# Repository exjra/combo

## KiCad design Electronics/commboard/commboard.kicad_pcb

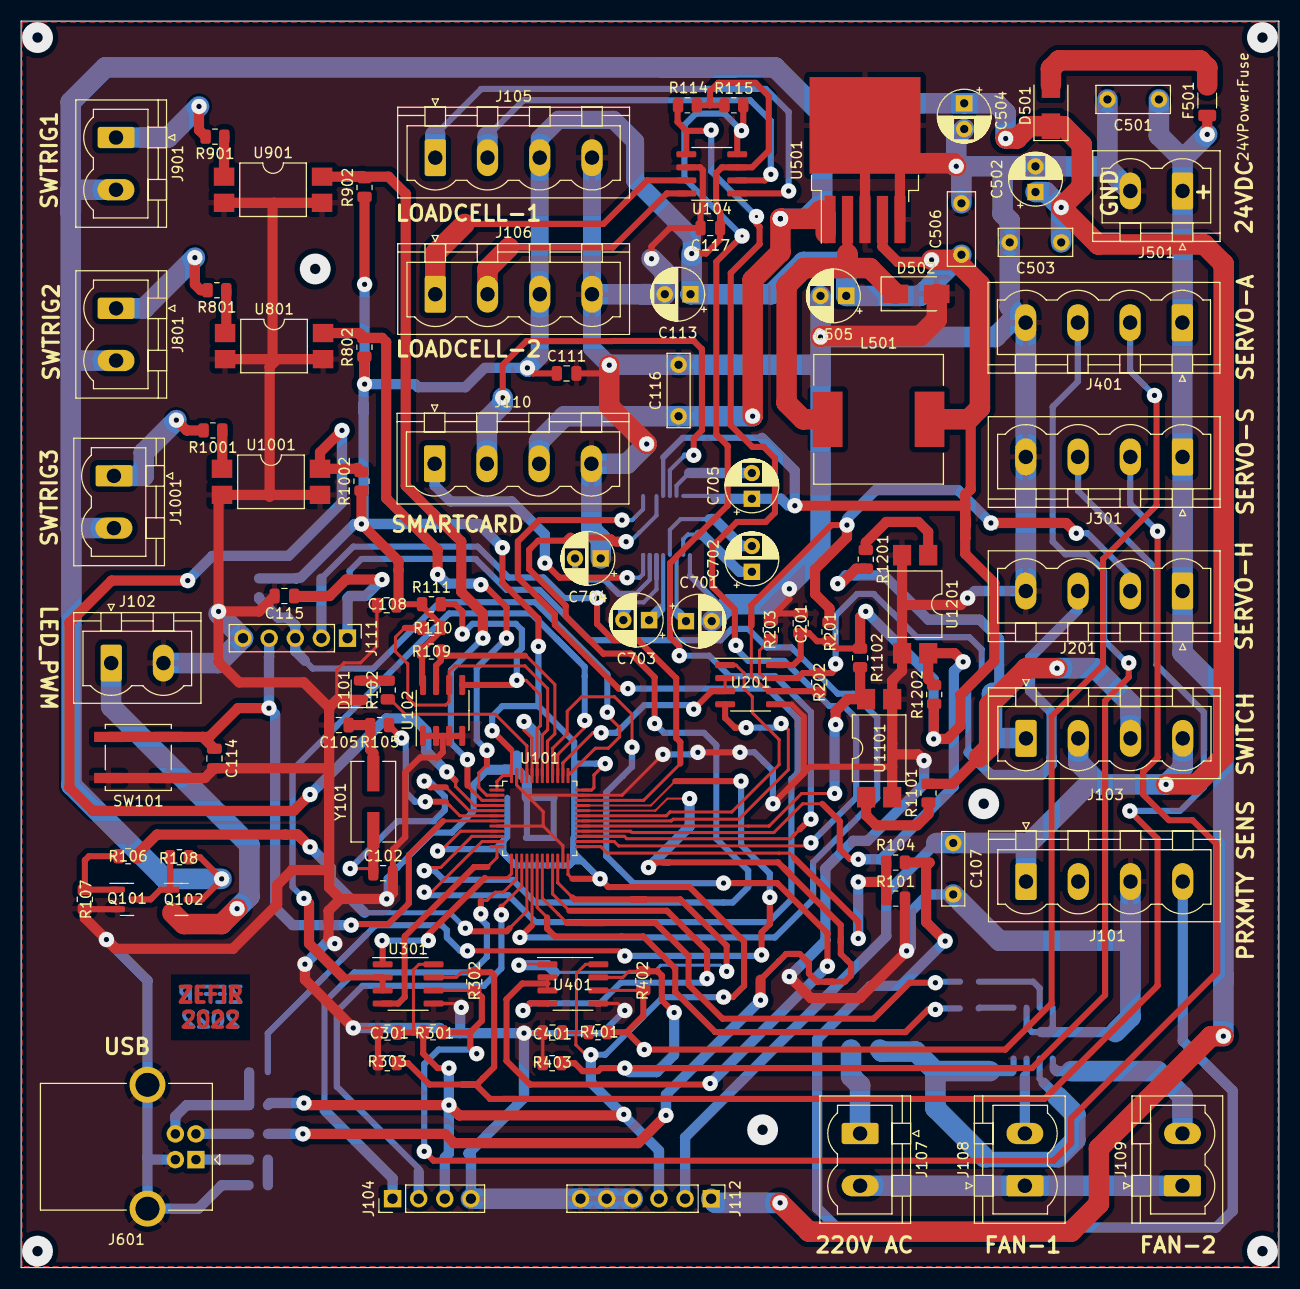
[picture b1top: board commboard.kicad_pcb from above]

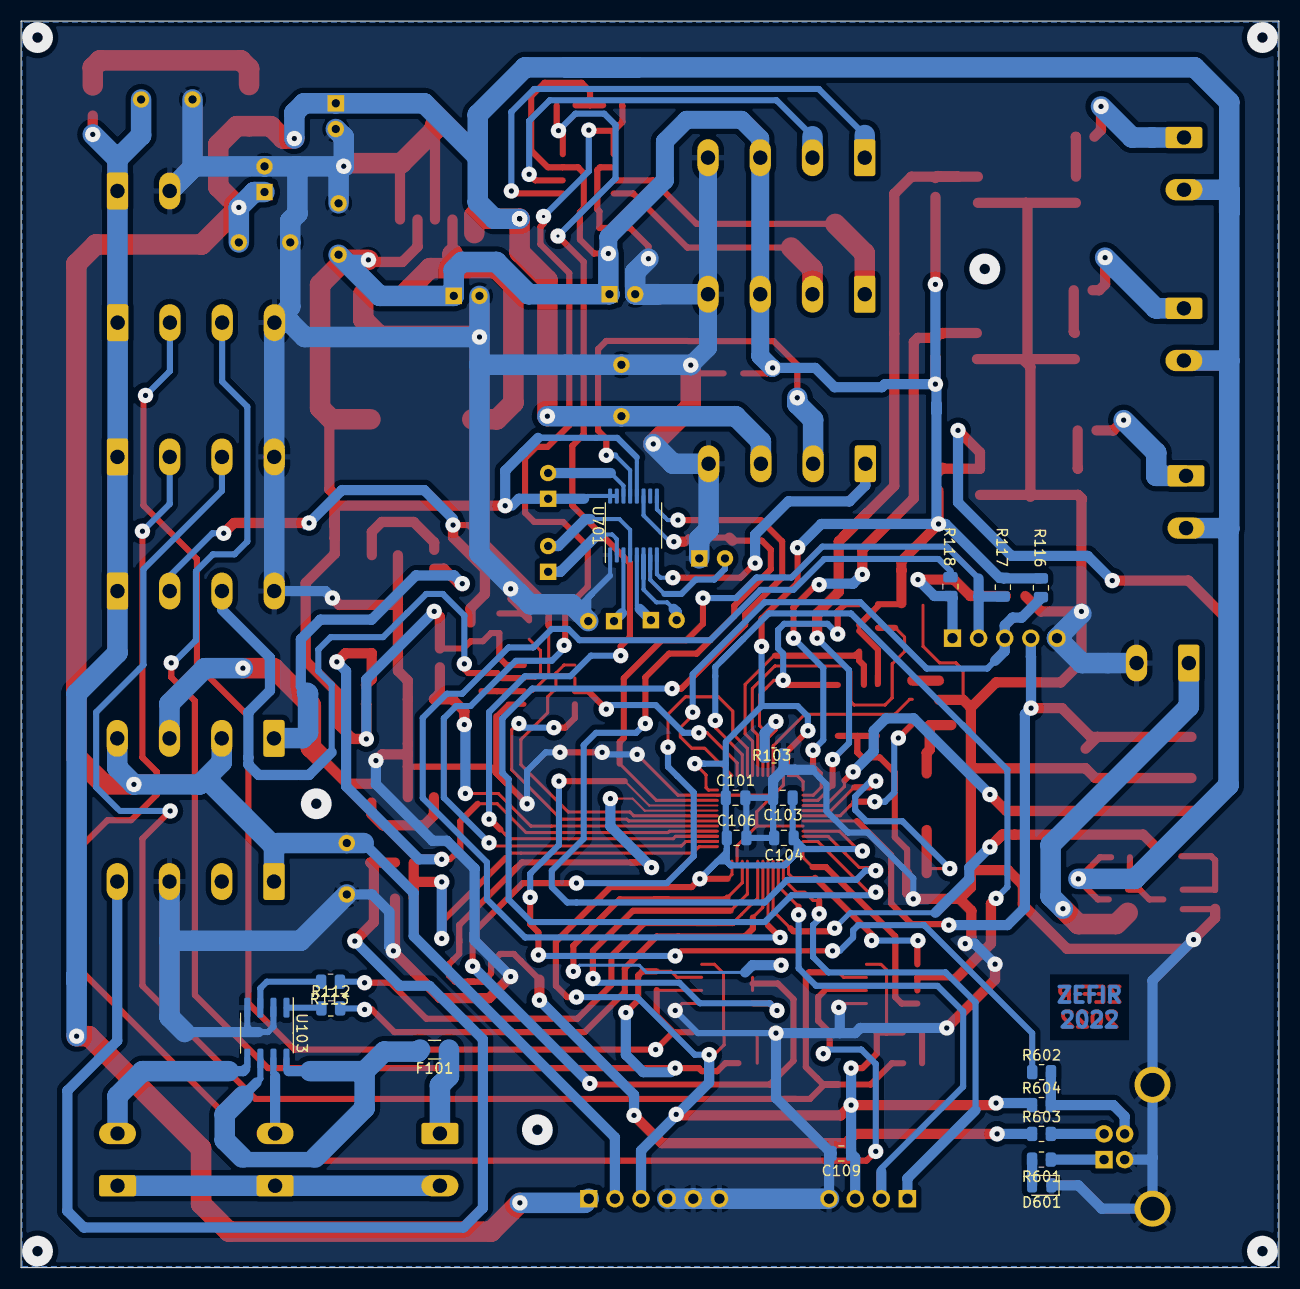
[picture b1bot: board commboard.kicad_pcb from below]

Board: 2 copper layers, 122.3 x 121.2 mm, 115 parts (19 on the bottom side), 90 nets.

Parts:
C101, C103, C104, C106, C108, C109, C111, C114, C115, C117, C201, C301, C401: 100nF; C_0805_2012Metric
C102, C105: 20pF; C_0805_2012Metric
C107, C116: 100nF; C_Rect_L7.0mm_W2.0mm_P5.00mm
C113, C504: 100uF; CP_Radial_D5.0mm_P2.50mm
C501, C503, C506: 100nF; C_Rect_L7.0mm_W2.5mm_P5.00mm
C502: 470uF; CP_Radial_D5.0mm_P2.50mm
C505: 1000uF; CP_Radial_D5.0mm_P2.50mm
C701, C702, C703, C704, C705: 0.1uF; CP_Radial_D5.0mm_P2.50mm
D101, D601: LED; D_0805_2012Metric
D501: SS36; D_SMA
D502: MBR360; D_SMA
F101: Fuse; Fuse_1206_3216Metric
F501: 24VPowerFuse; R_1206_3216Metric
J101: ProximitySensorConnector; PhoenixContact_MSTBVA_2,5_4-G-5,08_1x04_P5.08mm_Vertical
J102: PWM CONN; PhoenixContact_MSTBVA_2,5_2-G-5,08_1x02_P5.08mm_Vertical
J103: InputArray; PhoenixContact_MSTBVA_2,5_4-G-5,08_1x04_P5.08mm_Vertical
J104: ADC_Interface; PinHeader_1x04_P2.54mm_Vertical
J105: LC_Conn_1; PhoenixContact_MSTBVA_2,5_4-G-5,08_1x04_P5.08mm_Vertical
J106: LC_Conn_2; PhoenixContact_MSTBVA_2,5_4-G-5,08_1x04_P5.08mm_Vertical
J107: AC 220V; PhoenixContact_MSTBVA_2,5_2-G-5,08_1x02_P5.08mm_Vertical
J108: FAN1; PhoenixContact_MSTBVA_2,5_2-G-5,08_1x02_P5.08mm_Vertical
J109: FAN2; PhoenixContact_MSTBVA_2,5_2-G-5,08_1x02_P5.08mm_Vertical
J110: RS232_Out; PhoenixContact_MSTBVA_2,5_4-G-5,08_1x04_P5.08mm_Vertical
J111: STLINK; PinHeader_1x05_P2.54mm_Vertical
J112: Measurement Conn; PinHeader_1x06_P2.54mm_Vertical
J201, J301, J401: ServoConn; PhoenixContact_MSTBVA_2,5_4-G-5,08_1x04_P5.08mm_Vertical
J501: InputConn; PhoenixContact_MSTBVA_2,5_2-G-5,08_1x02_P5.08mm_Vertical
J601: USB_B; USB_B_OST_USB-B1HSxx_Horizontal
J801, J901, J1001: EXTINT_PORT_0; PhoenixContact_MSTBVA_2,5_2-G-5,08_1x02_P5.08mm_Vertical
L501: 100uH; L_12x12mm_H8mm
Q101: BC847; SOT-23
Q102: BSS83P; SOT-23
R101, R108, R802, R902, R1002, R1102, R1202: 4k7R; R_0805_2012Metric
R102, R601: 2k2R; R_0805_2012Metric
R103, R107: 10k; R_0805_2012Metric
R104: 620R; R_0805_2012Metric
R105: 390R; R_0805_2012Metric
R106, R118, R1101, R1201: 470R; R_0805_2012Metric
R109, R110, R111, R114, R115, R116, R117: 4k7; R_0805_2012Metric
R112, R113: 120R; R_0805_2012Metric
R201, R203, R301, R303, R401, R403: 220R; R_0805_2012Metric
R202, R302, R402: 60R; R_0805_2012Metric
R602, R603: 22R; R_0805_2012Metric
R604: 1k5R; R_0805_2012Metric
R801, R901, R1001: 1kR; R_0805_2012Metric
SW101: SW_Push; SW_Push_1P1T_NO_CK_KSC7xxJ
U101: STM32F070CBTx; LQFP-48_7x7mm_P0.5mm
U102: M24C08; SOIC-8_3.9x4.9mm_P1.27mm
U103: CPC1961GS; SOIC-8_3.9x4.9mm_P1.27mm
U104: MCP3426-xMC; SOIC-8_3.9x4.9mm_P1.27mm
U201, U301, U401: SP3485EN; SOIC-8_3.9x4.9mm_P1.27mm
U501: LM2576HVS-3.3; TO-263-5_TabPin3
U701: MAX3221; TSSOP-16_4.4x5mm_P0.65mm
U801, U901, U1001, U1101, U1201: LTV-817S; SMDIP-4_W9.53mm
Y101: 8MHz; Crystal_SMD_ECS_CSM3X-2Pin_7.6x4.1mm

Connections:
24V_Safe: C107.1, C116.1, C502.1, C503.1, C504.1, D501.1 (K), J101.1, J103.2, J103.4, J110.3, J112.2, J801.2, J901.2, J1001.2, Q102.3 (D), R108.1, U501.1 (VIN)
24V_Unsafe: C501.1, F501.1, J112.1, J201.1, J301.1, J401.1, J501.1
+3.3V: C101.1, C103.1, C104.1, C106.1, C108.1, C109.1, C111.1, C113.1, C117.1, C201.1, C301.1, C401.1, C505.1, C506.1, C705.1, J104.3, J105.3, J106.3, J112.3, L501.2, R109.1, R110.1, R111.1, R114.1, R115.1, R116.1, R117.1, R201.1, R301.1, R401.1, R604.1, R802.1, R902.1, R1002.1, R1102.1, R1202.1, U101.1 (VDD), U101.9 (VDDA), U101.24 (VDD), U101.36 (VDD), U101.48 (VDD), U102.8 (VCC), U104.3 (VDD), U201.8 (VCC), U301.8 (VCC), U401.8 (VCC), U501.4 (FB), U701.12 (FORCEON), U701.15 (Vcc), U701.16 (FORCEOFF)
/InputModuleNC3/SW: J103.1, R1201.2
/InputModuleNC/SW: J103.3, R1101.2
/RS232Interface/RS232_In: J110.1, U701.8 (RIN)
/RS232Interface/RS232_Out: J110.2, U701.13 (DOUT)
AC_DRV1: R112.2, U101.18 (PB0)
AC_DRV2: R113.2, U101.19 (PB1)
ADC0: J104.1, U101.14 (PA4)
ADC1: J104.2, U101.15 (PA5)
DebuggerSens: R118.2, U101.17 (PA7)
EEPROM_SCL: R110.2, U101.42 (PB6), U102.6 (SCL)
EEPROM_SDA: R111.2, U101.43 (PB7), U102.5 (SDA)
EEPROM_WRP: R109.2, U101.41 (PB5), U102.7 (~WC)
EXTINT0: R802.2, U101.2 (PC13), U801.4
EXTINT1: R902.2, U101.3 (PC14), U901.4
EXTINT2: R1002.2, U101.4 (PC15), U1001.4
GND: C101.2, C102.2, C103.2, C104.2, C105.2, C106.2, C107.2, C108.2, C109.2, C111.2, C113.2, C114.2, C115.2, C116.2, C117.2, C201.2, C301.2, C401.2, C501.2, C502.2, C503.2, C504.2, C505.2, C506.2, C701.2, C704.1, D101.1 (K), D502.2 (A), D601.1 (K), J101.3, J102.2, J104.4, J105.4, J106.4, J110.4, J111.5, J112.4, J112.5, J112.6, J201.4, J301.4, J401.4, J501.2, J601.4 (GND), J601.5 (Shield), Q101.2 (E), R101.2, R103.2, R107.2, R203.2, R303.2, R403.2, SW101.2, U101.8 (VSSA), U101.23 (VSS), U101.35 (VSS), U101.47 (VSS), U102.1 (E0), U102.2 (E1), U102.3 (E2), U102.4 (VSS), U103.2 (-LED1), U103.4 (-LED2), U104.6 (VSS), U201.5 (GND), U301.5 (GND), U401.5 (GND), U501.3 (GND), U501.5 (~ON/OFF), U701.1 (EN), U801.2, U801.3, U901.2, U901.3, U1001.2, U1001.3, U1101.2, U1101.3, U1201.2, U1201.3
LOADCELL_SCL: R114.2, U101.26 (PB13), U104.5 (SCL)
LOADCELL_SDA: R115.2, U101.27 (PB14), U104.4 (SDA)
LedPWMPin: R106.1, U101.16 (PA6)
NRST: C114.1, J111.4, SW101.1, U101.7 (NRST)
unnamed: C102.1, U101.5 (PF0), Y101.1
unnamed: C105.1, R105.2, Y101.2
unnamed: C701.1, U701.3 (V+)
unnamed: C702.1, U701.2 (C1+)
unnamed: C702.2, U701.4 (C1-)
unnamed: C703.1, U701.5 (C2+)
unnamed: C703.2, U701.6 (C2-)
unnamed: C704.2, U701.7 (V-)
unnamed: C705.2, U701.14 (GND)
unnamed: D101.2 (A), R102.2
unnamed: D501.2 (A), F501.2
unnamed: D502.1 (K), L501.1, U501.2 (OUT)
unnamed: D601.2 (A), R601.2
unnamed: J101.4, R104.1
unnamed: J102.1, Q102.2 (S)
unnamed: J105.1, U104.1 (CH1+)
unnamed: J105.2, U104.2 (CH1-)
unnamed: J106.1, U104.7 (CH2+)
unnamed: J106.2, U104.8 (CH2-)
unnamed: F101.1, J107.1
unnamed: J107.2, J108.1, J109.1
unnamed: J108.2, U103.7 (ACLoad)
unnamed: J109.2, U103.5 (ACLoad)
unnamed: C115.1, J111.1, R118.1
unnamed: J201.2, R201.2, R202.1, U201.6 (A)
unnamed: J201.3, R202.2, R203.1, U201.7 (B)
unnamed: J301.2, R301.2, R302.1, U301.6 (A)
unnamed: J301.3, R302.2, R303.1, U301.7 (B)
unnamed: J401.2, R401.2, R402.1, U401.6 (A)
unnamed: J401.3, R402.2, R403.1, U401.7 (B)
unnamed: J601.1 (VBUS), R601.1
unnamed: J601.2 (D-), R603.2
unnamed: J601.3 (D+), R602.2, R604.2
unnamed: J801.1, R801.2
unnamed: J901.1, R901.2
unnamed: J1001.1, R1001.2
unnamed: Q101.1 (B), R106.2, R107.1
unnamed: Q101.3 (C), Q102.1 (G), R108.2
unnamed: R102.1, U101.45 (PB8)
unnamed: R103.1, U101.44 (BOOT0)
unnamed: R105.1, U101.6 (PF1)
unnamed: R112.1, U103.1 (+LED1)
unnamed: R113.1, U103.3 (+LED2)
unnamed: R801.1, U801.1
unnamed: R901.1, U901.1
unnamed: R1001.1, U1001.1
unnamed: R1101.1, U1101.1
unnamed: R1201.1, U1201.1
unnamed: F101.2, U103.6 (ACLoad), U103.8 (ACLoad)
RS232_Rx: U101.11 (PA1), U701.9 (ROUT)
RS232_Tx: U101.10 (PA0), U701.11 (DIN)
RS4851_Control1: U101.38 (PA15), U201.2 (~RE), U201.3 (DE)
RS4851_Control2: U101.39 (PB3), U301.2 (~RE), U301.3 (DE)
RS4851_Control3: U101.40 (PB4), U401.2 (~RE), U401.3 (DE)
RS4851_Rx1: U101.31 (PA10), U201.1 (RO)
RS4851_Rx2: U101.13 (PA3), U301.1 (RO)
RS4851_Rx3: U101.22 (PB11), U401.1 (RO)
RS4851_Tx1: U101.30 (PA9), U201.4 (DI)
RS4851_Tx2: U101.12 (PA2), U301.4 (DI)
RS4851_Tx3: U101.21 (PB10), U401.4 (DI)
SWCLK: J111.3, R116.2, U101.37 (PA14)
SWDIO: J111.2, R117.2, U101.34 (PA13)
SW_In0: R1202.2, U101.28 (PB15), U1201.4
SW_In1: R1102.2, U101.29 (PA8), U1101.4
USBD+: R602.1, U101.33 (PA12)
USBD-: R603.1, U101.32 (PA11)
objectSensorPin: R101.1, R104.2, U101.25 (PB12)

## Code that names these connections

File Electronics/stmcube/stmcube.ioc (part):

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Mcu.Name=STM32F070CBTx
Mcu.Package=LQFP48
Mcu.UserName=STM32F070CBTx
PA0.GPIOParameters=GPIO_Label
PA0.GPIO_Label=RS232_Tx
PA0.Mode=Asynchronous
PA0.Signal=USART4_TX
PA1.GPIOParameters=GPIO_Label
PA1.GPIO_Label=RS232_Rx
PA1.Mode=Asynchronous
PA1.Signal=USART4_RX
PA10.Mode=Asynchronous
PA10.Signal=USART1_RX
PA11.Mode=Device
PA11.Signal=USB_DM
PA12.Mode=Device
PA12.Signal=USB_DP
PA13.Mode=Serial_Wire
PA13.Signal=SYS_SWDIO
PA14.Mode=Serial_Wire
PA14.Signal=SYS_SWCLK
PA15.GPIOParameters=GPIO_Label
PA15.GPIO_Label=RS485_Control1
PA15.Signal=GPIO_Output
PA2.Mode=Asynchronous
PA2.Signal=USART2_TX
PA3.Mode=Asynchronous
PA3.Signal=USART2_RX
PA4.GPIOParameters=GPIO_Label
PA4.GPIO_Label=ADC0
PA4.Mode=IN4
PA4.Signal=ADC_IN4
PA5.GPIOParameters=GPIO_Label
PA5.GPIO_Label=ADC1
PA5.Mode=IN5
PA5.Signal=ADC_IN5
PA6.GPIOParameters=GPIO_Label
PA6.GPIO_Label=PWMLedOut
PA6.Signal=S_TIM3_CH1
PA7.GPIOParameters=GPIO_Label
PA7.GPIO_Label=DebuggerSens
PA7.Signal=GPIO_Input
PA8.GPIOParameters=GPIO_Label
PA8.GPIO_Label=SW_In1
PA8.Signal=GPIO_Input
PA9.Mode=Asynchronous
PA9.Signal=USART1_TX
PB0.GPIOParameters=GPIO_Label
PB0.GPIO_Label=AC_DRV1
PB0.Signal=GPIO_Output
PB1.GPIOParameters=GPIO_Label
PB1.GPIO_Label=AC_DRV2
PB1.Signal=GPIO_Output
PB10.Mode=Asynchronous
PB10.Signal=USART3_TX
PB11.Mode=Asynchronous
PB11.Signal=USART3_RX
PB12.GPIOParameters=GPIO_Label
PB12.GPIO_Label=objectSensorPin
PB12.Signal=GPIO_Input
PB13.GPIOParameters=GPIO_Label
PB13.GPIO_Label=LOADCELL_SCL
PB13.Mode=I2C
PB13.Signal=I2C2_SCL
PB14.GPIOParameters=GPIO_Label
PB14.GPIO_Label=LOADCELL_SDA
PB14.Mode=I2C
PB14.Signal=I2C2_SDA
PB15.GPIOParameters=GPIO_Label
PB15.GPIO_Label=SW_In0
PB15.Signal=GPIO_Input
PB3.GPIOParameters=GPIO_Label
PB3.GPIO_Label=RS485_Control2
PB3.Signal=GPIO_Output
PB4.GPIOParameters=GPIO_Label
PB4.GPIO_Label=RS485_Control3
PB4.Signal=GPIO_Output
PB5.GPIOParameters=GPIO_Label
PB5.GPIO_Label=EEPROM_WRP
PB5.Signal=GPIO_Output
PB6.GPIOParameters=GPIO_Label
PB6.GPIO_Label=EEPROM_SCL
PB6.Mode=I2C
PB6.Signal=I2C1_SCL
PB7.GPIOParameters=GPIO_Label
PB7.GPIO_Label=EEPROM_SDA
PB7.Mode=I2C
PB7.Signal=I2C1_SDA
PB8.GPIOParameters=GPIO_Label
PB8.GPIO_Label=DebugLed
PB8.Signal=GPIO_Output
PC13.GPIOParameters=GPIO_Label
PC13.GPIO_Label=EXTINT0
PC13.Signal=GPXTI13
PC14-OSC32_IN.GPIOParameters=GPIO_Label
PC14-OSC32_IN.GPIO_Label=EXTINT1
PC14-OSC32_IN.Signal=GPXTI14
PC15-OSC32_OUT.GPIOParameters=GPIO_Label
PC15-OSC32_OUT.GPIO_Label=EXTINT2
PC15-OSC32_OUT.Signal=GPXTI15
PF0-OSC_IN.Mode=HSE-External-Oscillator
PF0-OSC_IN.Signal=RCC_OSC_IN
PF1-OSC_OUT.Mode=HSE-External-Oscillator
PF1-OSC_OUT.Signal=RCC_OSC_OUT
RCC.SYSCLKFreq_VALUE=48000000
RCC.SYSCLKSource=RCC_SYSCLKSOURCE_PLLCLK
board=custom

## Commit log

2022-10-17 initial commit.
2022-10-18 completed pcb design
2022-10-21 schematic design completed. pcb layout drawings completed.
